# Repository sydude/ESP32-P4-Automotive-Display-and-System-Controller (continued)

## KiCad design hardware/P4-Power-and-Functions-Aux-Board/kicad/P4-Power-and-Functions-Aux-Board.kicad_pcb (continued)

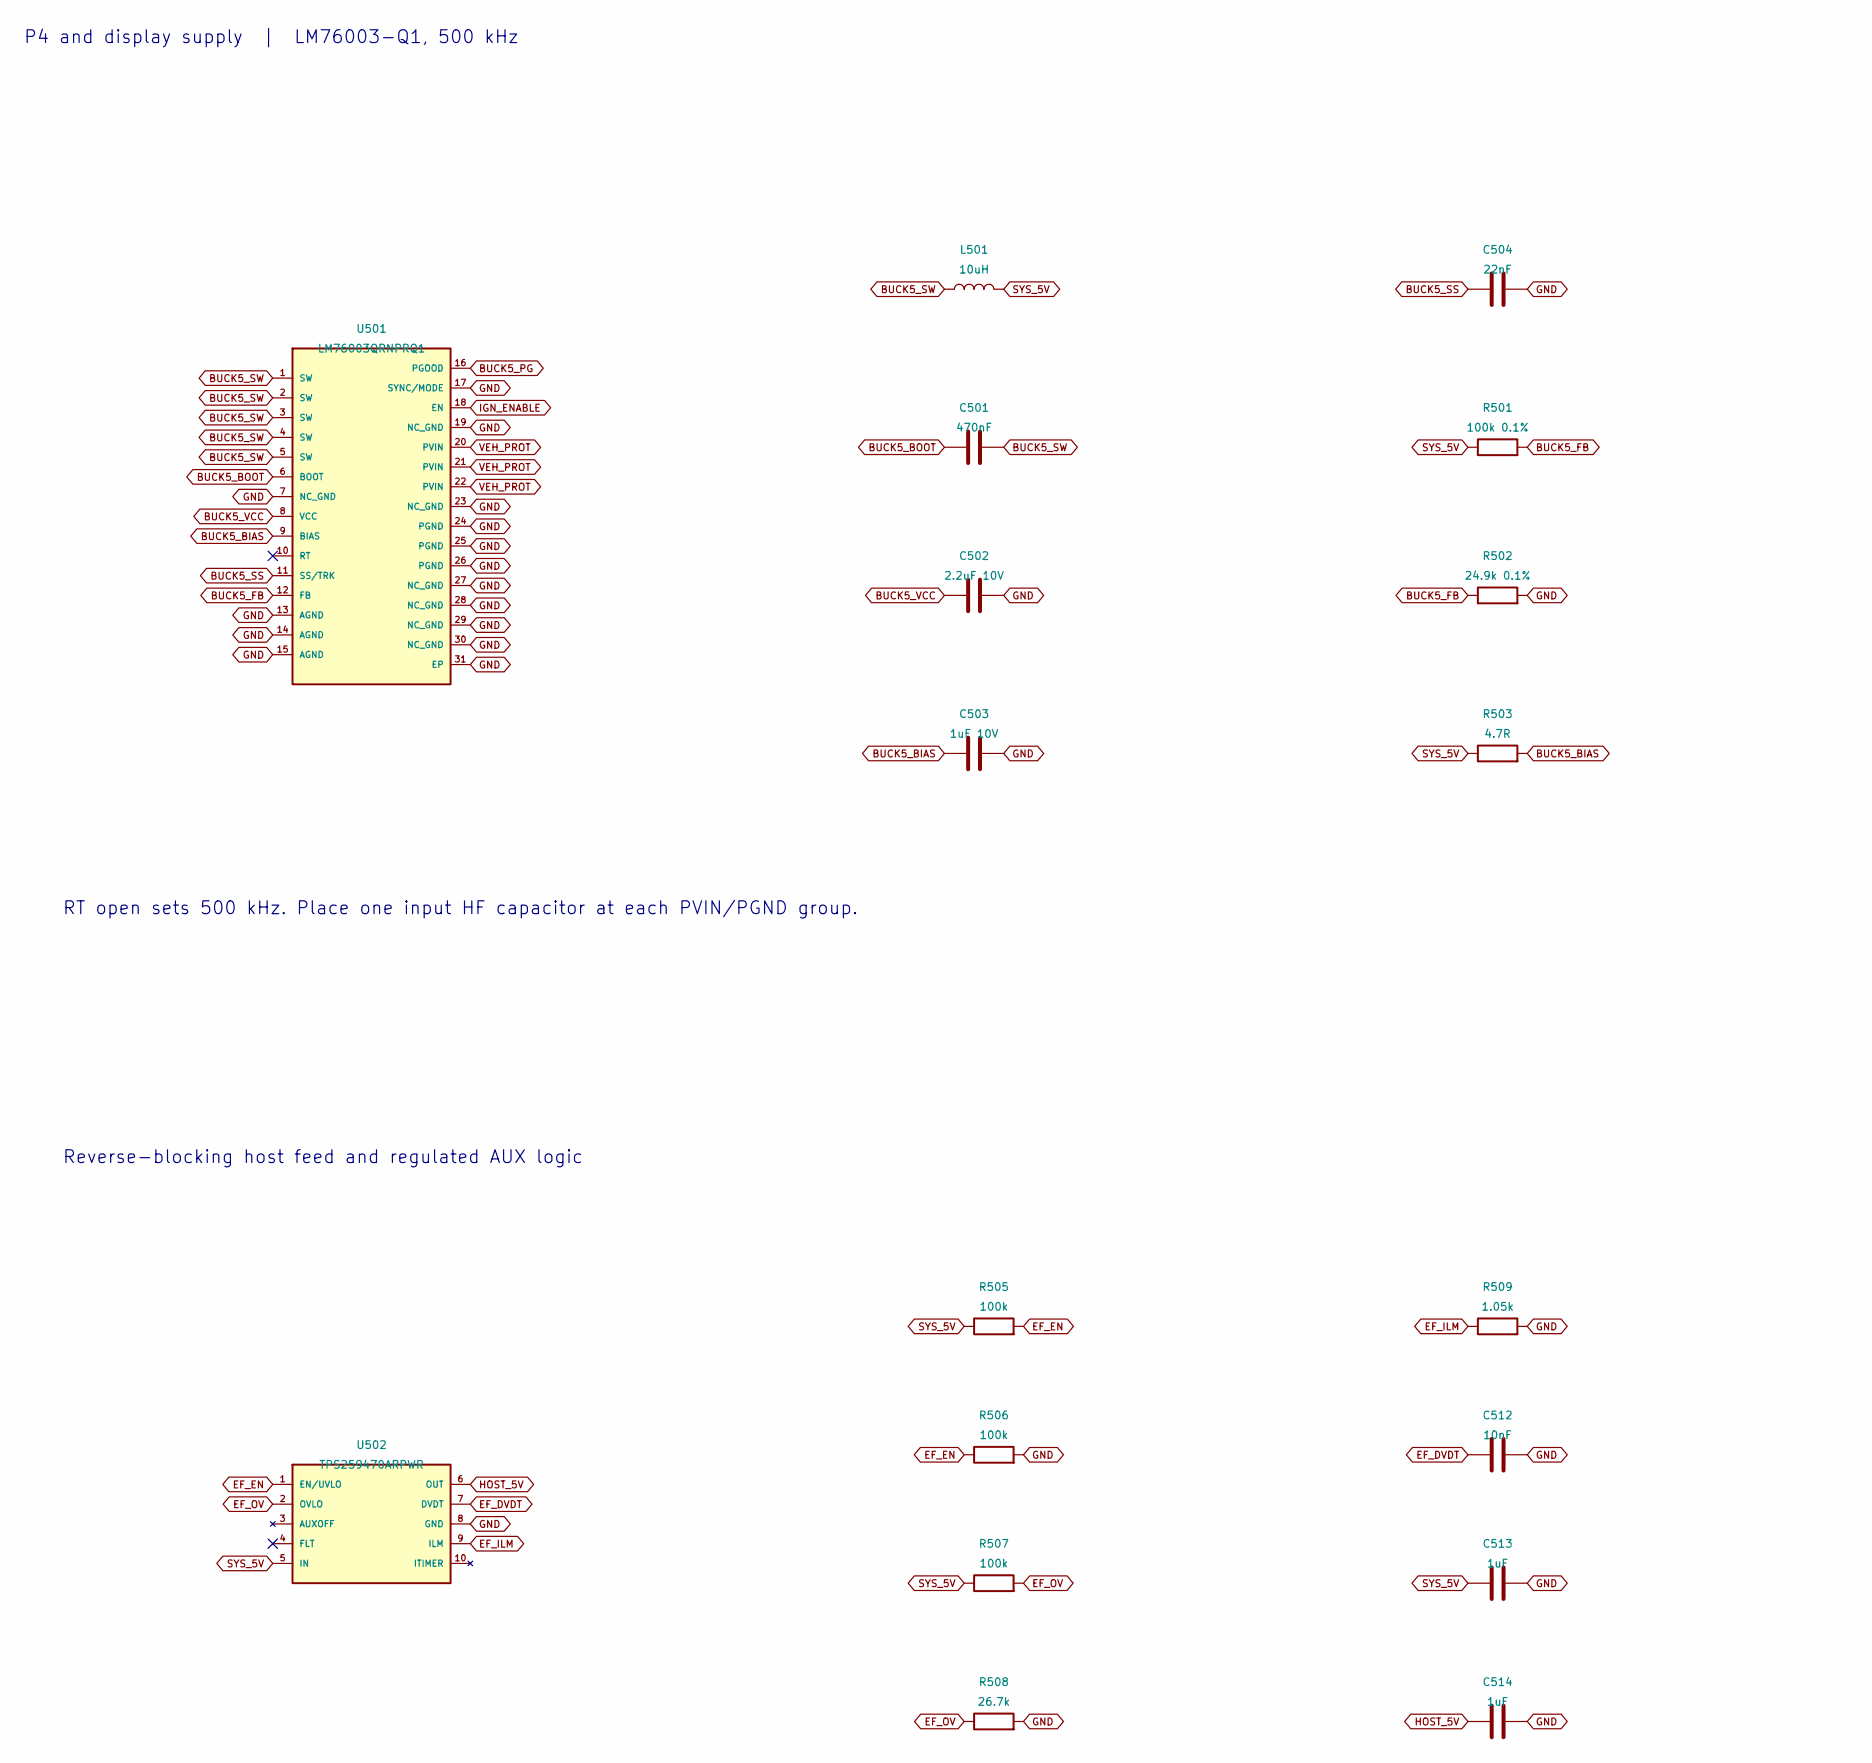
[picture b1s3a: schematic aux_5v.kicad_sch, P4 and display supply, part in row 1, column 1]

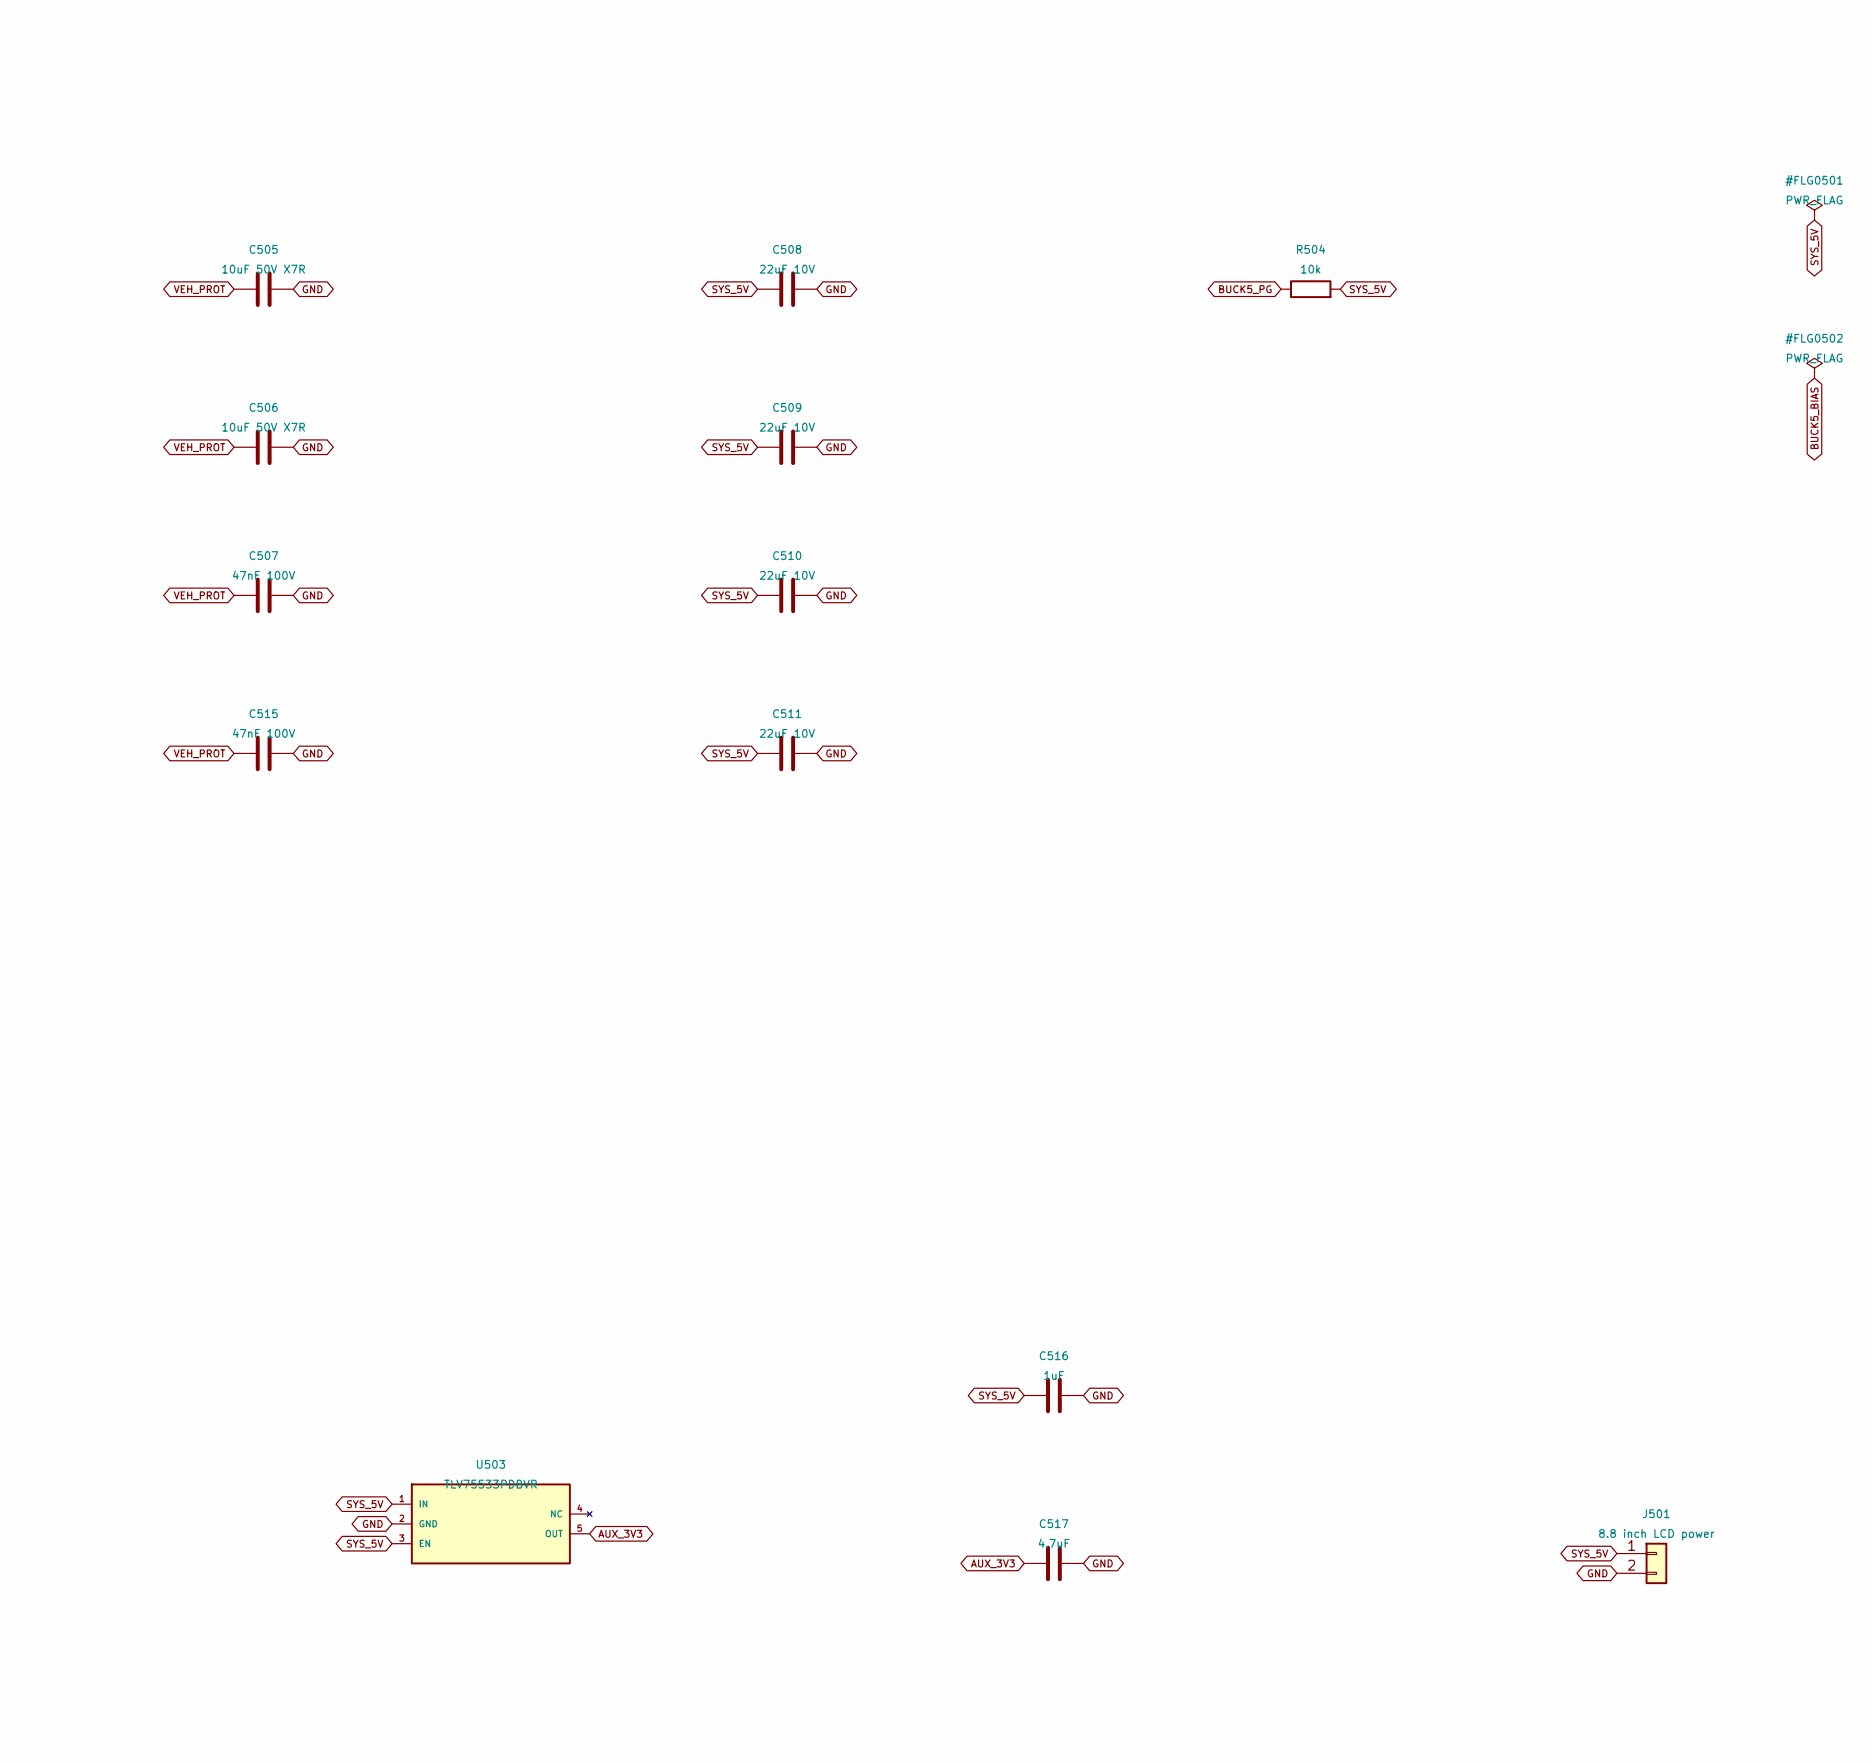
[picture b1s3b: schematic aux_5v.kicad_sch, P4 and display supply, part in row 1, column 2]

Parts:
C501: 470nF; C_0603_1608Metric; MPN GRM188R71E474KA12D; LCSC C77052
C502: 2.2uF 10V; C_0603_1608Metric; MPN GRM188R71A225KE15D; LCSC C86018
C503: 1uF 10V; C_0603_1608Metric; MPN GCM188R71C105KA64D; LCSC C161212
C504: 22nF; C_0603_1608Metric; MPN GRM188R71H223KA01D; LCSC C77056
C505, C506: 10uF 50V X7R; C_1210_3225Metric; MPN GRM32ER71H106KA12L; LCSC C77102
C507, C515: 47nF 100V; C_0603_1608Metric; MPN C0603C473K1RAC7867; LCSC C3881354
C508, C509, C510, C511: 22uF 10V; C_1210_3225Metric; MPN GCM32ER71A226KE12L; LCSC C913632
C512: 10nF; C_0603_1608Metric; MPN GCM188R71H103KA37D; LCSC C85863
C513, C514, C516: 1uF; C_0603_1608Metric; MPN GCM188R71C105KA64D; LCSC C161212
C517: 4.7uF; C_0603_1608Metric; MPN GRM188R61A475KE15D; LCSC C71633
J501: 8.8 inch LCD power; Molex_SL_171971-0002_1x02_P2.54mm_Vertical; MPN 171971-0002
L501: 10uH; L_Coilcraft_XAL7070-XXX; MPN XAL7070-103MEC; LCSC C55598417
R501: 100k 0.1%; R_0603_1608Metric; MPN RT0603BRD07100KL; LCSC C122538
R502: 24.9k 0.1%; R_0603_1608Metric; MPN TR0603B24K9P0525Z; LCSC C149931
R503: 4.7R; R_0603_1608Metric; MPN AC0603FR-074R7L; LCSC C144651
R504: 10k; R_0603_1608Metric; MPN AC0603FR-0710KL; LCSC C116677
R505, R506, R507: 100k; R_0603_1608Metric; MPN AC0603FR-07100KL; LCSC C116674
R508: 26.7k; R_0603_1608Metric; MPN RC0603FR-0726K7L; LCSC C137756
R509: 1.05k; R_0603_1608Metric; MPN ERJ-3EKF1051V; LCSC C402872
U501: LM76003QRNPRQ1; Texas_RNP0030B_WQFN-30-1EP_4x6mm_P0.5mm_EP1.8x4.5mm_Thermal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; MPN LM76003QRNPRQ1; LCSC C2073028
U502: TPS259470ARPWR; Texas_RPW0010A_VQFN-HR-10_2x2mm; MPN TPS259470ARPWR; LCSC C3662799
U503: TLV75533PDBVR; SOT-23-5; MPN TLV75533PDBVR; LCSC C404027

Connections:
AUX_3V3: C517.1, U503.5 (OUT); also elsewhere on the board
BUCK5_BIAS: C503.1, R503.2, U501.9 (BIAS)
BUCK5_BOOT: C501.1, U501.6 (BOOT)
BUCK5_FB: R501.2, R502.1, U501.12 (FB)
BUCK5_PG: R504.1, U501.16 (PGOOD)
BUCK5_SS: C504.1, U501.11 (SS/TRK)
BUCK5_SW: C501.2, L501.1, U501.1 (SW), U501.2 (SW), U501.3 (SW), U501.4 (SW), U501.5 (SW)
BUCK5_VCC: C502.1, U501.8 (VCC)
EF_DVDT: C512.1, U502.7 (DVDT)
EF_EN: R505.2, R506.1, U502.1 (EN/UVLO)
EF_ILM: R509.1, U502.9 (ILM)
EF_OV: R507.2, R508.1, U502.2 (OVLO)
GND: C502.2, C503.2, C504.2, C505.2, C506.2, C507.2, C508.2, C509.2, C510.2, C511.2, C512.2, C513.2, C514.2, C515.2, C516.2, C517.2, J501.2, R502.2, R506.2, R508.2, R509.2, U501.7 (NC_GND), U501.13 (AGND), U501.14 (AGND), U501.15 (AGND), U501.17 (SYNC/MODE), U501.19 (NC_GND), U501.23 (NC_GND), U501.24 (PGND), U501.25 (PGND), U501.26 (PGND), U501.27 (NC_GND), U501.28 (NC_GND), U501.29 (NC_GND), U501.30 (NC_GND), U501.31 (EP), U502.8 (GND), U503.2 (GND); also elsewhere on the board
HOST_5V: C514.1, U502.6 (OUT); also elsewhere on the board
IGN_ENABLE: U501.18 (EN); also elsewhere on the board
SYS_5V: C508.1, C509.1, C510.1, C511.1, C513.1, C516.1, J501.1, L501.2, R501.1, R503.1, R504.2, R505.1, R507.1, U502.5 (IN), U503.1 (IN), U503.3 (EN); also elsewhere on the board
VEH_PROT: C505.1, C506.1, C507.1, C515.1, U501.20 (PVIN), U501.21 (PVIN), U501.22 (PVIN); also elsewhere on the board

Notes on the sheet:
RT open sets 500 kHz. Place one input HF capacitor at each PVIN/PGND group.
P4 and display supply | LM76003-Q1, 500 kHz
Reverse-blocking host feed and regulated AUX logic

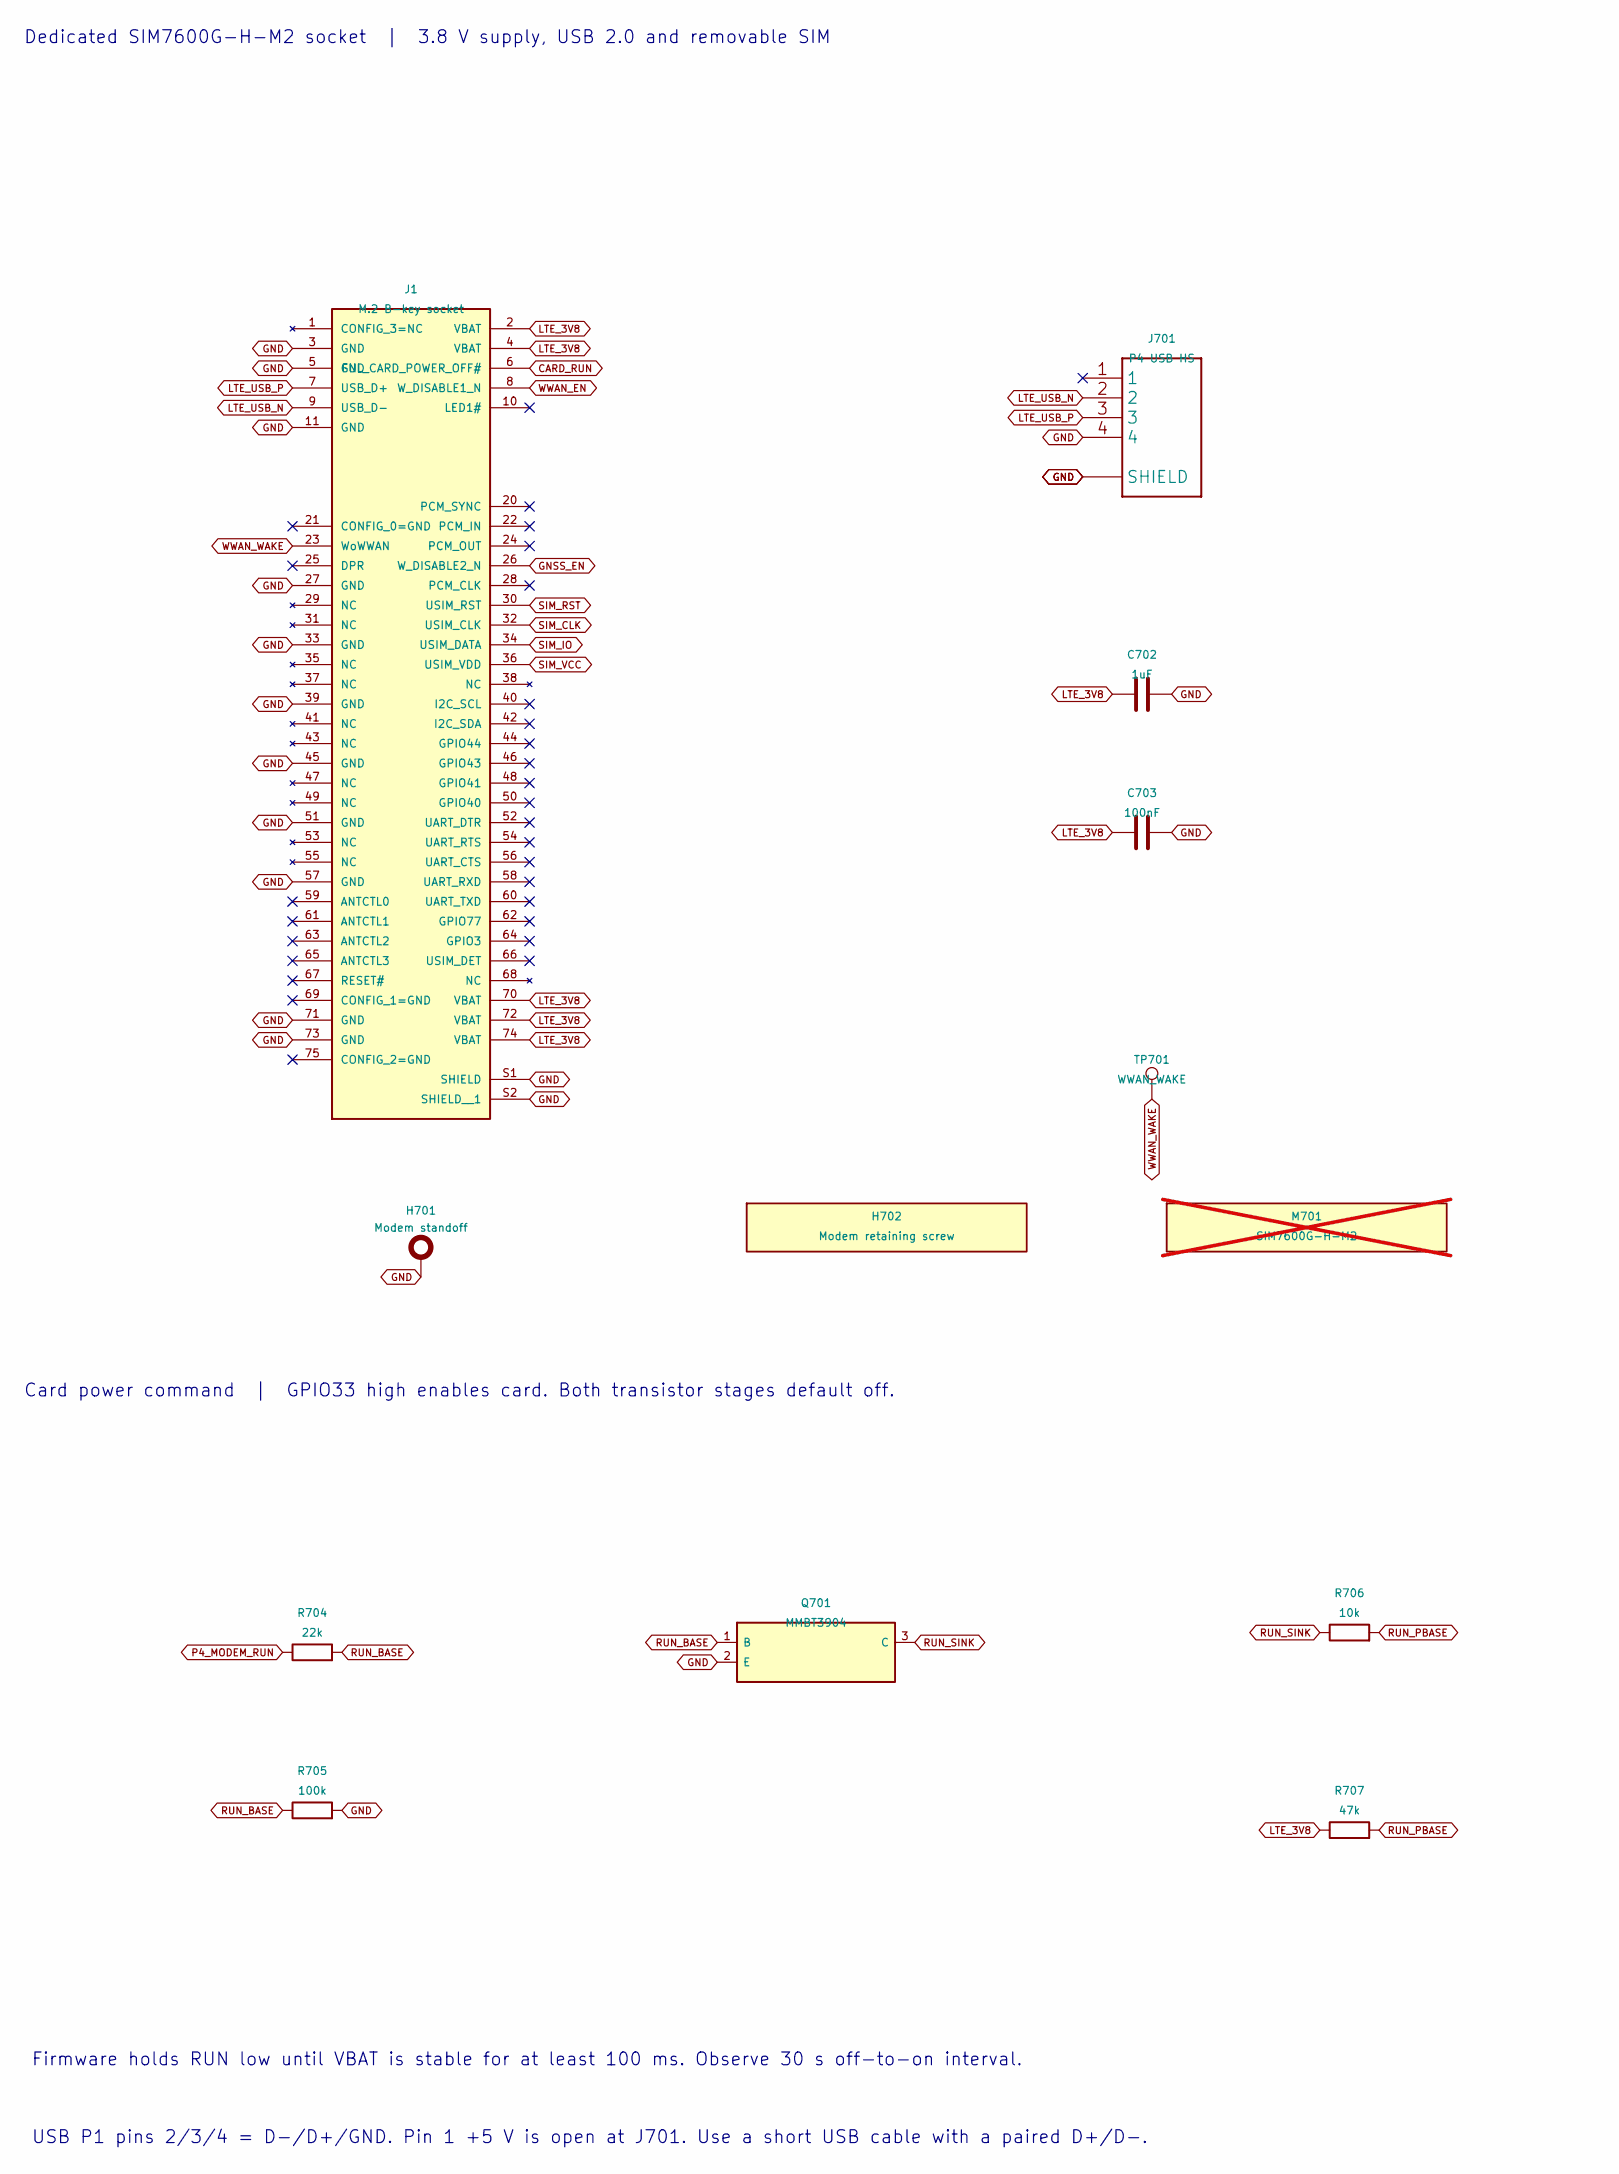
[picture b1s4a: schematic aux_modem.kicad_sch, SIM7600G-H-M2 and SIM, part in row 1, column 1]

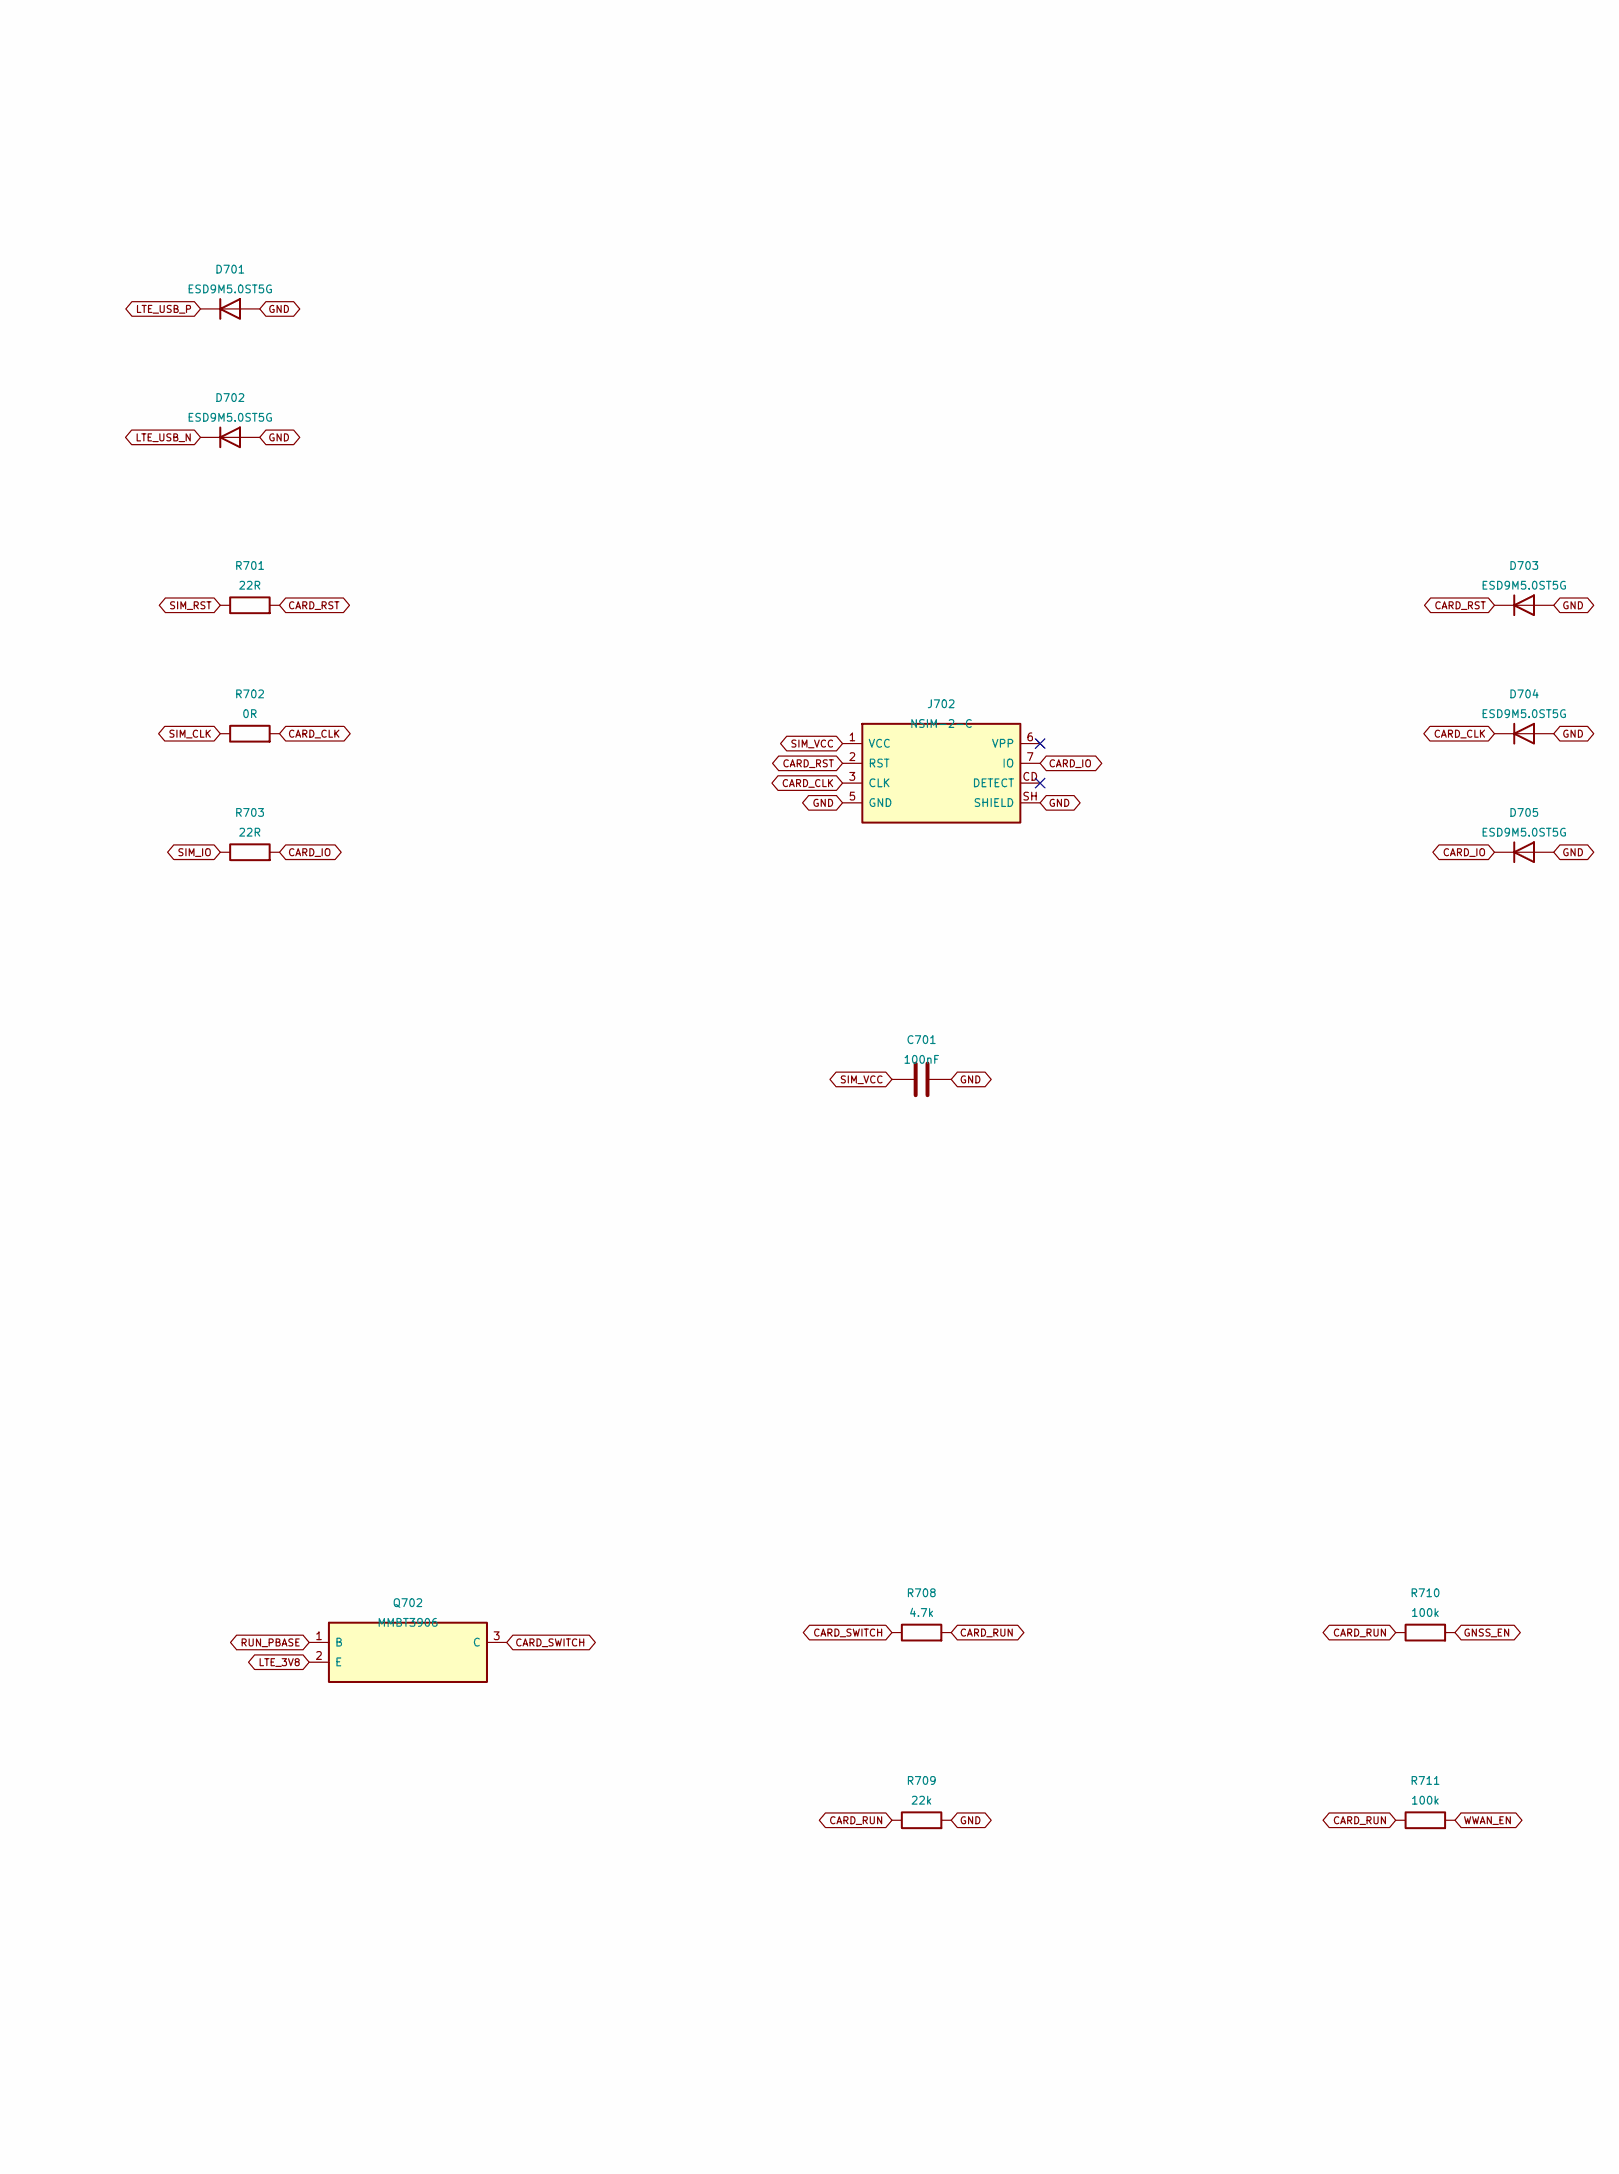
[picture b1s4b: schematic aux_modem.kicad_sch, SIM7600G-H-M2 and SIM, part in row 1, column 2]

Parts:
C701, C703: 100nF; C_0603_1608Metric; MPN GCM188R71C104KA37D; LCSC C184760
C702: 1uF; C_0603_1608Metric; MPN GCM188R71C105KA64D; LCSC C161212
D701, D702, D703, D704, D705: ESD9M5.0ST5G; D_SOD-923; MPN ESD9M5.0ST5G; LCSC C242267
H701: Modem standoff; JAE_SM3ZS067U410-NUT1; MPN SM3ZS067U410-NUT1-R1200; LCSC C5137457
H702: Modem retaining screw; MPN CM2X3-4.5
J1: M.2 B-key socket; AMPHENOL_MDT420B01001; MPN MDT420B01001; LCSC C4594496
J701: P4 USB HS; JST_BM04B-GHS-TBT_Vertical; MPN BM04B-GHS-TBT(LF)(SN); LCSC C161692
J702: NSIM-2-C; nanoSIM_Hinged_CUI_NSIM-2-C; MPN NSIM-2-C; LCSC C29799059
M701: SIM7600G-H-M2; MPN SIM7600G-H-M2; not fitted
Q701: MMBT3904; SOT-23; MPN MMBT3904-7-F; LCSC C94514
Q702: MMBT3906; SOT-23; MPN MMBT3906-7-F; LCSC C82762
R701, R703: 22R; R_0603_1608Metric; MPN AC0603FR-0722RL; LCSC C138283
R702: 0R; R_0603_1608Metric; MPN RC0603JR-070RL; LCSC C95177
R704, R709: 22k; R_0603_1608Metric; MPN AC0603FR-0722KL; LCSC C144680
R705, R710, R711: 100k; R_0603_1608Metric; MPN AC0603FR-07100KL; LCSC C116674
R706: 10k; R_0603_1608Metric; MPN AC0603FR-0710KL; LCSC C116677
R707: 47k; R_0603_1608Metric; MPN AC0603FR-0747KL; LCSC C111134
R708: 4.7k; R_0603_1608Metric; MPN AC0603FR-074K7L; LCSC C116697
TP701: WWAN_WAKE; TestPoint_Pad_D1.0mm

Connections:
CARD_CLK: D704.1 (K), J702.3 (CLK), R702.2
CARD_IO: D705.1 (K), J702.7 (IO), R703.2
CARD_RST: D703.1 (K), J702.2 (RST), R701.2
CARD_RUN: J1.6 (FUL_CARD_POWER_OFF#), R708.2, R709.1, R710.1, R711.1
CARD_SWITCH: Q702.3 (C), R708.1
GND: C701.2, C702.2, C703.2, D701.2 (A), D702.2 (A), D703.2 (A), D704.2 (A), D705.2 (A), H701.1 (GND), J1.3 (GND), J1.5 (GND), J1.11 (GND), J1.27 (GND), J1.33 (GND), J1.39 (GND), J1.45 (GND), J1.51 (GND), J1.57 (GND), J1.71 (GND), J1.73 (GND), J1.S1 (SHIELD), J1.S2 (SHIELD__1), J701.4, J701.SH1 (SHIELD), J701.SH2 (SHIELD), J702.5 (GND), J702.SH (SHIELD), Q701.2 (E), R705.2, R709.2; also elsewhere on the board
GNSS_EN: J1.26 (W_DISABLE2_N), R710.2
LTE_3V8: C702.1, C703.1, J1.2 (VBAT), J1.4 (VBAT), J1.70 (VBAT), J1.72 (VBAT), J1.74 (VBAT), Q702.2 (E), R707.1; also elsewhere on the board
LTE_USB_N: D702.1 (K), J1.9 (USB_D-), J701.2
LTE_USB_P: D701.1 (K), J1.7 (USB_D+), J701.3
P4_MODEM_RUN: R704.1; also elsewhere on the board
RUN_BASE: Q701.1 (B), R704.2, R705.1
RUN_PBASE: Q702.1 (B), R706.2, R707.2
RUN_SINK: Q701.3 (C), R706.1
SIM_CLK: J1.32 (USIM_CLK), R702.1
SIM_IO: J1.34 (USIM_DATA), R703.1
SIM_RST: J1.30 (USIM_RST), R701.1
SIM_VCC: C701.1, J1.36 (USIM_VDD), J702.1 (VCC)
WWAN_EN: J1.8 (W_DISABLE1_N), R711.2
WWAN_WAKE: J1.23 (WoWWAN), TP701.1 (1_1)

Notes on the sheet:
Card power command | GPIO33 high enables card. Both transistor stages default off.
USB P1 pins 2/3/4 = D-/D+/GND. Pin 1 +5 V is open at J701. Use a short USB cable with a paired D+/D-.
Dedicated SIM7600G-H-M2 socket | 3.8 V supply, USB 2.0 and removable SIM
Firmware holds RUN low until VBAT is stable for at least 100 ms. Observe 30 s off-to-on interval.
